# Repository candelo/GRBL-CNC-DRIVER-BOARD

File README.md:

# GRBL-CNC-DRIVER-BOARD
GRBL Driver PCB based on A4988 and Arduino ATMEGA328P Stepper driver and Arduino one layer PCB for milling.

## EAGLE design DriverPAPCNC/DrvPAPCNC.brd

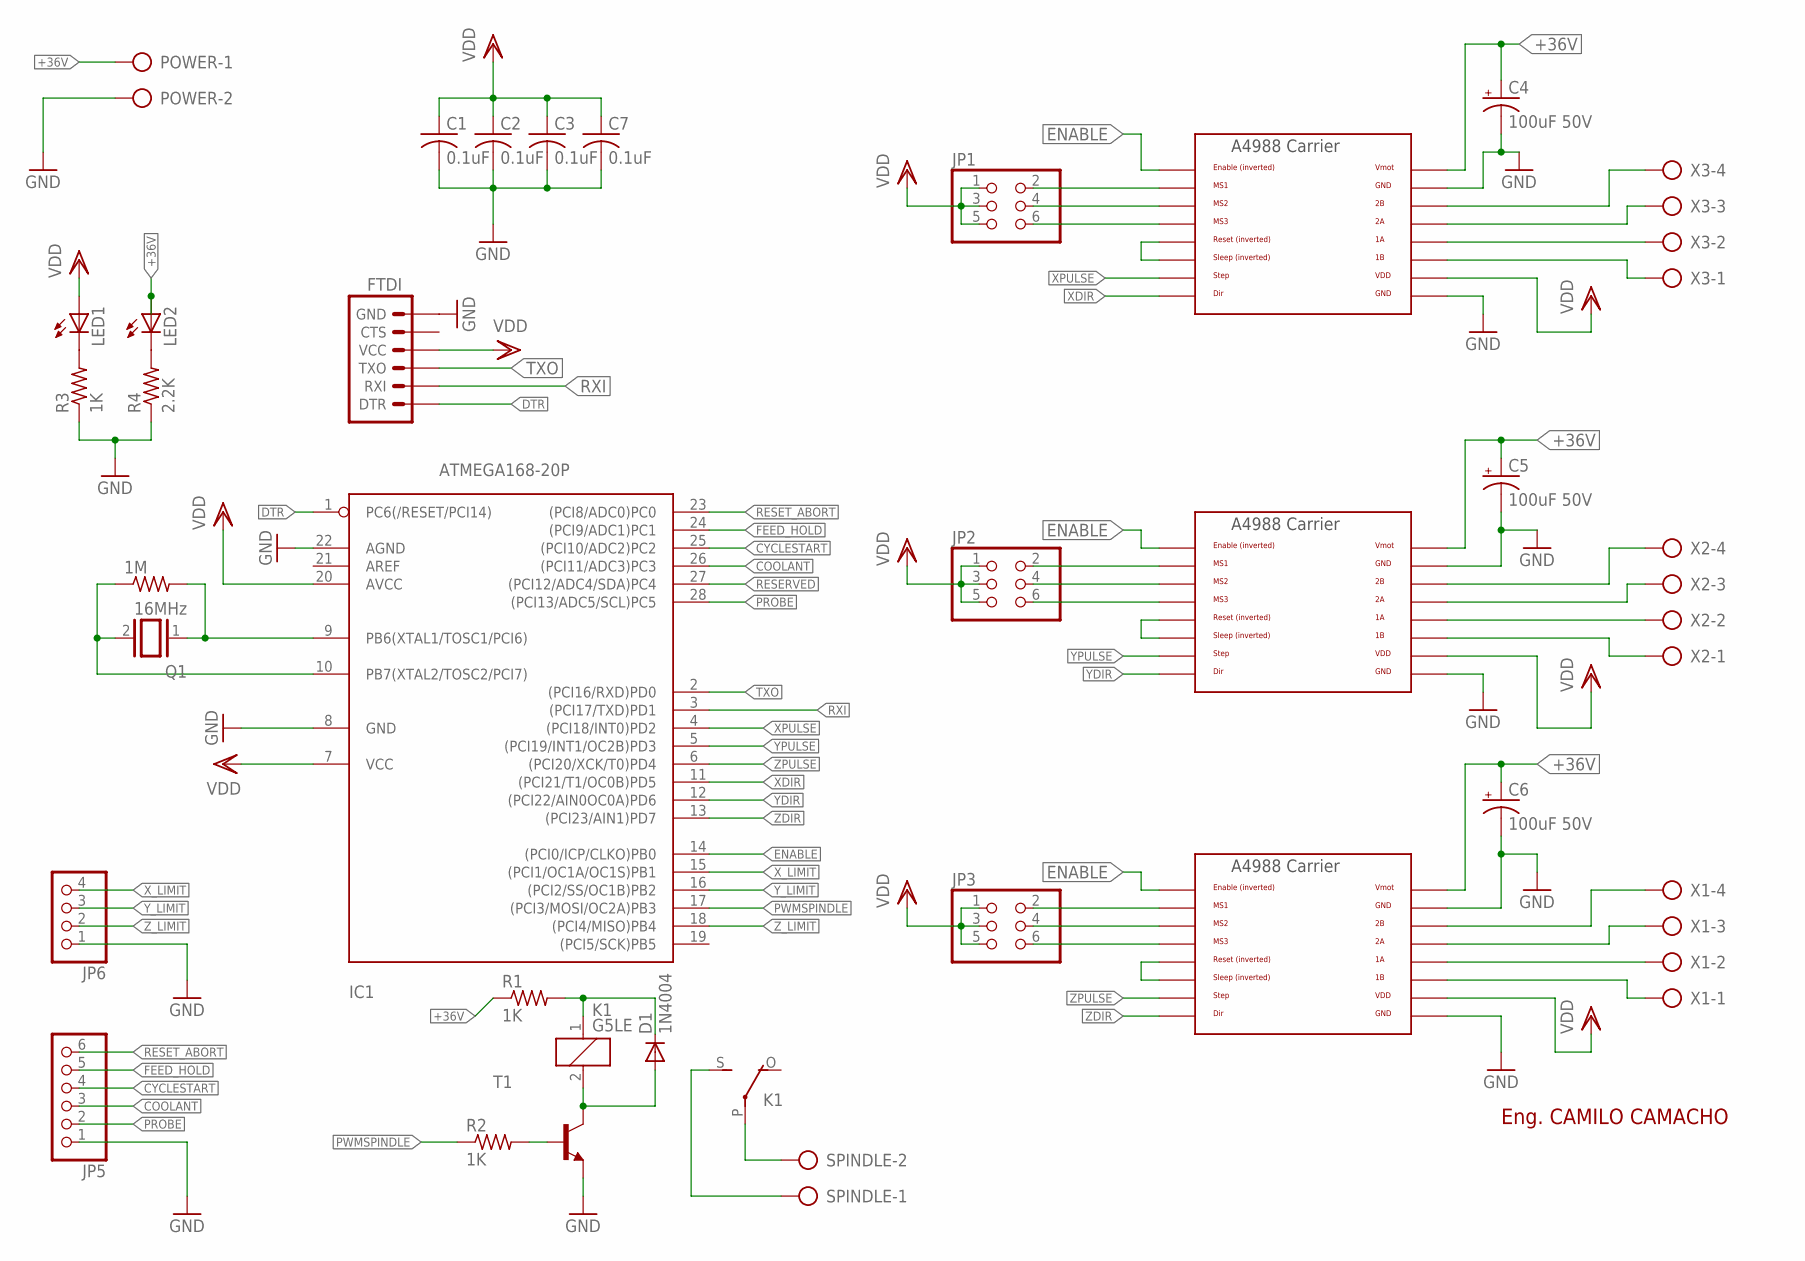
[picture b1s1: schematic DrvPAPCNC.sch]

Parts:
1M: R-US_0204/2V; 0204V
C1, C2, C3, C7: 0.1uF; C025-025X050
C4, C5, C6: 100uF 50V; E7,5-16
D1: 1N4004; DO41-10
FTDI: ARDUINO_SERIAL_PROGRAMPTH; 1X06
IC1: ATMEGA168-20P; DIL28-3
JP1, JP2, JP3: PINHD-2X3; 2X03
JP5: PINHD-1X6; 1X06
JP6: PINHD-1X4; 1X04
K1: G5LE
LED1, LED2: LED5MM
POWER: AK300/2
Q1: 16MHz; QS
R1, R2, R3: 1K; 0207/10
R4: 2.2K; 0207/10
SPINDLE: AK300/2
T1: 2N3904-NPN-TO92-EBC; TO92-EBC
U$1, U$2, U$3: A4988BREAKOUT
X1, X2, X3: AK300/4

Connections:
+36V: C4.+, C5.+, C6.+, LED2.A, POWER.1, R1.1, U$1.VMOT, U$2.VMOT, U$3.VMOT
COOLANT: IC1.26 ((PCI11/ADC3)PC3), JP5.3
CYCLESTART: IC1.25 ((PCI10/ADC2)PC2), JP5.4
DTR: FTDI.1 (DTR), IC1.1 (PC6(/RESET/PCI14))
ENABLE: IC1.14 ((PCI0/ICP/CLKO)PB0), U$1.EN, U$2.EN, U$3.EN
FEED_HOLD: IC1.24 ((PCI9/ADC1)PC1), JP5.5
GND: C1.2, C2.2, C3.2, C4.-, C5.-, C6.-, C7.2, FTDI.6 (GND), IC1.8 (GND), IC1.22 (AGND), JP5.1, JP6.1, POWER.2, R3.1, R4.1, T1.E, U$1.GND, U$1.GND@0 (GND), U$2.GND, U$2.GND@0 (GND), U$3.GND, U$3.GND@0 (GND)
unnamed: U$1.2B, X3.4
unnamed: U$1.2A, X3.3
unnamed: U$1.1A, X3.2
unnamed: U$1.1B, X3.1
unnamed: U$2.1B, X2.1
unnamed: U$2.1A, X2.2
unnamed: U$2.2A, X2.3
unnamed: U$2.2B, X2.4
unnamed: U$3.2B, X1.4
unnamed: U$3.2A, X1.3
unnamed: U$3.1A, X1.2
unnamed: U$3.1B, X1.1
unnamed: K1.P, SPINDLE.2
unnamed: K1.S, SPINDLE.1
unnamed: JP1.2, U$1.MS1
unnamed: JP1.4, U$1.MS2
unnamed: JP1.6, U$1.MS3
unnamed: JP2.2, U$2.MS1
unnamed: JP2.4, U$2.MS2
unnamed: JP2.6, U$2.MS3
unnamed: JP3.2, U$3.MS1
unnamed: JP3.4, U$3.MS2
unnamed: JP3.6, U$3.MS3
unnamed: U$3.RST, U$3.SLP (SLEEP)
unnamed: U$2.RST, U$2.SLP (SLEEP)
unnamed: U$1.RST, U$1.SLP (SLEEP)
unnamed: D1.C, K1.1, R1.2
unnamed: D1.A, K1.2, T1.C
unnamed: 1M.2, IC1.9 (PB6(XTAL1/TOSC1/PCI6)), Q1.1
unnamed: 1M.1, IC1.10 (PB7(XTAL2/TOSC2/PCI7)), Q1.2
unnamed: R2.2, T1.B
unnamed: LED1.K (C), R3.2
unnamed: LED2.K (C), R4.2
PROBE: IC1.28 ((PCI13/ADC5/SCL)PC5), JP5.2
PWMSPINDLE: IC1.17 ((PCI3/MOSI/OC2A)PB3), R2.1
RESERVED: IC1.27 ((PCI12/ADC4/SDA)PC4)
RESET_ABORT: IC1.23 ((PCI8/ADC0)PC0), JP5.6
RXI: FTDI.2 (RXI), IC1.3 ((PCI17/TXD)PD1)
TXO: FTDI.3 (TXO), IC1.2 ((PCI16/RXD)PD0)
VDD: C1.1, C2.1, C3.1, C7.1, FTDI.4 (VCC), IC1.7 (VCC), IC1.20 (AVCC), JP1.1, JP1.3, JP1.5, JP2.1, JP2.3, JP2.5, JP3.1, JP3.3, JP3.5, LED1.A, U$1.VDD, U$2.VDD, U$3.VDD
XDIR: IC1.11 ((PCI21/T1/OC0B)PD5), U$1.DIR
XPULSE: IC1.4 ((PCI18/INT0)PD2), U$1.STEP
X_LIMIT: IC1.15 ((PCI1/OC1A/OC1S)PB1), JP6.4
YDIR: IC1.12 ((PCI22/AIN0OC0A)PD6), U$2.DIR
YPULSE: IC1.5 ((PCI19/INT1/OC2B)PD3), U$2.STEP
Y_LIMIT: IC1.16 ((PCI2/SS/OC1B)PB2), JP6.3
ZDIR: IC1.13 ((PCI23/AIN1)PD7), U$3.DIR
ZPULSE: IC1.6 ((PCI20/XCK/T0)PD4), U$3.STEP
Z_LIMIT: IC1.18 ((PCI4/MISO)PB4), JP6.2

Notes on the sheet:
Eng. CAMILO CAMACHO

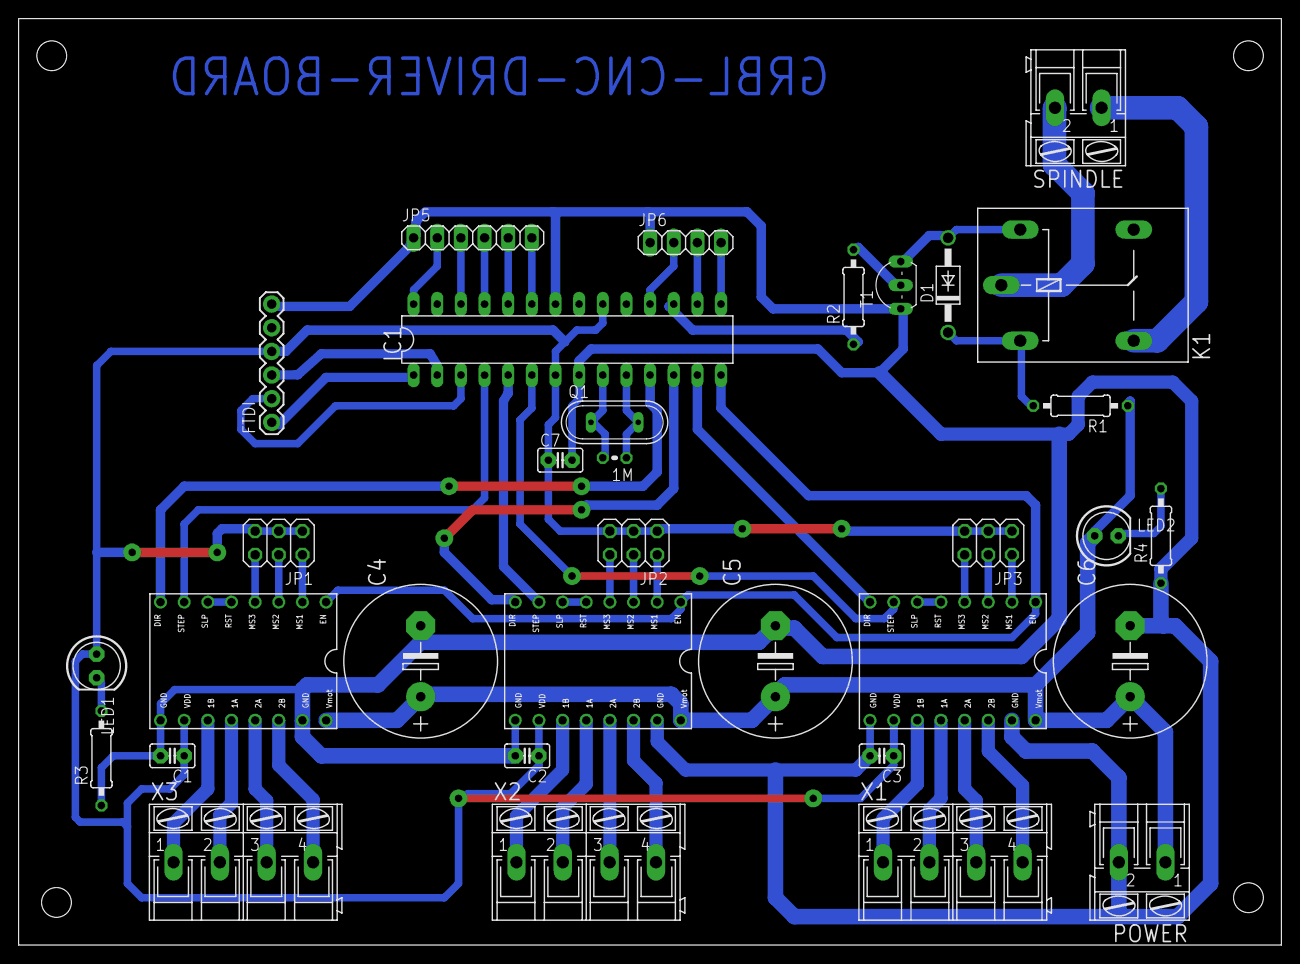
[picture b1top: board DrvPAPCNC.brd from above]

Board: 2 copper layers, 135.6 x 99.5 mm, 33 parts (0 on the bottom side), 55 nets.

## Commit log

2015-11-15 Add Schematic and board files
    Add Schematic and board files
2015-11-16 Finish Route PCB one layer
    Finish Route PCB one layer.

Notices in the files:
parts and their libraries:
SparkFun-Connectors: Licensing: Creative Commons ShareAlike 4.0 International - https://creativecommons.org/licenses/by-sa/4.0
